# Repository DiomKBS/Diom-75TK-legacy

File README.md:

# full-board-shorter
a keyboard with 75% layout that has macrokeys and a numpad

## The current design:

## You can visit the whiteboard over at Milanote:
Link --> [Whiteboard](https://app.milanote.com/1NjfUT1bPf1Z3v?p=4XtU1EYbywI)

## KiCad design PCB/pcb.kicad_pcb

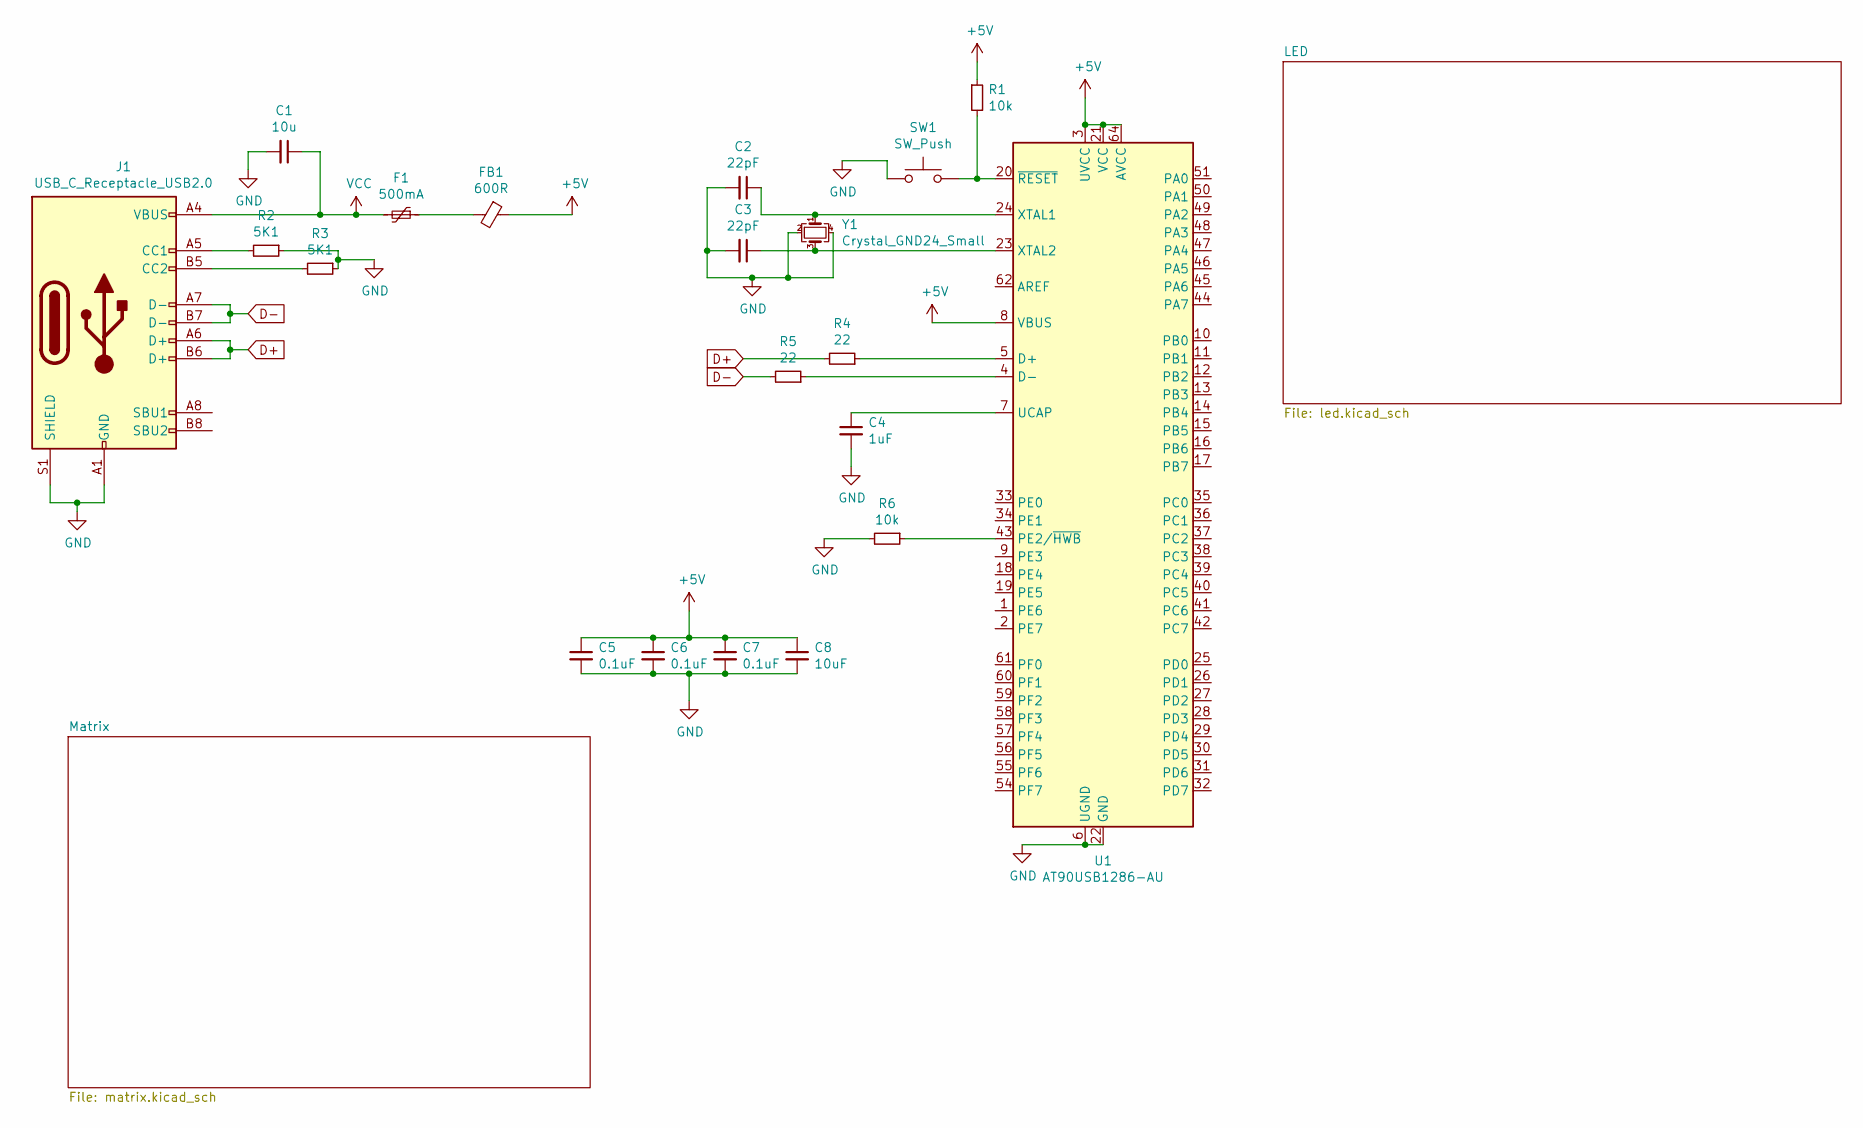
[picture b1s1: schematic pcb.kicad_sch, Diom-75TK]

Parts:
C1: 10u; C_0805_2012Metric
C2, C3: 22pF; C_0805_2012Metric
C4: 1uF; C_0805_2012Metric
C5, C6, C7: 0.1uF; C_0805_2012Metric
C8: 10uF; C_0805_2012Metric
F1: 500mA; Fuse_1206_3216Metric
FB1: 600R; Ferrite_Bead_0603
J1: USB_C_Receptacle_USB2.0; USB_C_Receptacle_HRO_TYPE-C-31-M-12
R1, R6: 10k; R_0805_2012Metric
R2, R3: 5K1; R_0805_2012Metric
R4, R5: 22; R_0805_2012Metric
SW1: SW_Push; switch_without_switch
U1: AT90USB1286-AU; TQFP-64_14x14mm_P0.8mm
Y1: Crystal_GND24_Small; Crystal_SMD_3225-4Pin_3.2x2.5mm

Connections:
+5V: C5.1, C6.1, C7.1, C8.1, FB1.1, R1.1, U1.3 (UVCC), U1.8 (VBUS), U1.21 (VCC), U1.52 (VCC), U1.64 (AVCC); also elsewhere on the board
D+: J1.A6 (D+), J1.B6 (D+), R4.2
D-: J1.A7 (D-), J1.B7 (D-), R5.2
GND: C1.2, C2.2, C3.2, C4.2, C5.2, C6.2, C7.2, C8.2, J1.A1 (GND), J1.A12 (GND), J1.B1 (GND), J1.B12 (GND), J1.S1 (SHIELD), R2.1, R3.1, R6.2, SW1.1, U1.6 (UGND), U1.22 (GND), U1.53 (GND), U1.63 (GND), Y1.2, Y1.4; also elsewhere on the board
unnamed: C2.1, U1.24 (XTAL1), Y1.1
unnamed: C3.1, U1.23 (XTAL2), Y1.3
unnamed: C4.1, U1.7 (UCAP)
unnamed: F1.1, FB1.2
unnamed: J1.A5 (CC1), R2.2
unnamed: J1.B5 (CC2), R3.2
unnamed: R1.2, SW1.2, U1.20 (~RESET)
unnamed: R4.1, U1.5 (D+)
unnamed: R5.1, U1.4 (D-)
unnamed: R6.1, U1.43 (PE2/~HWB)
VCC: C1.1, F1.2, J1.A4 (VBUS), J1.A9 (VBUS), J1.B4 (VBUS), J1.B9 (VBUS)

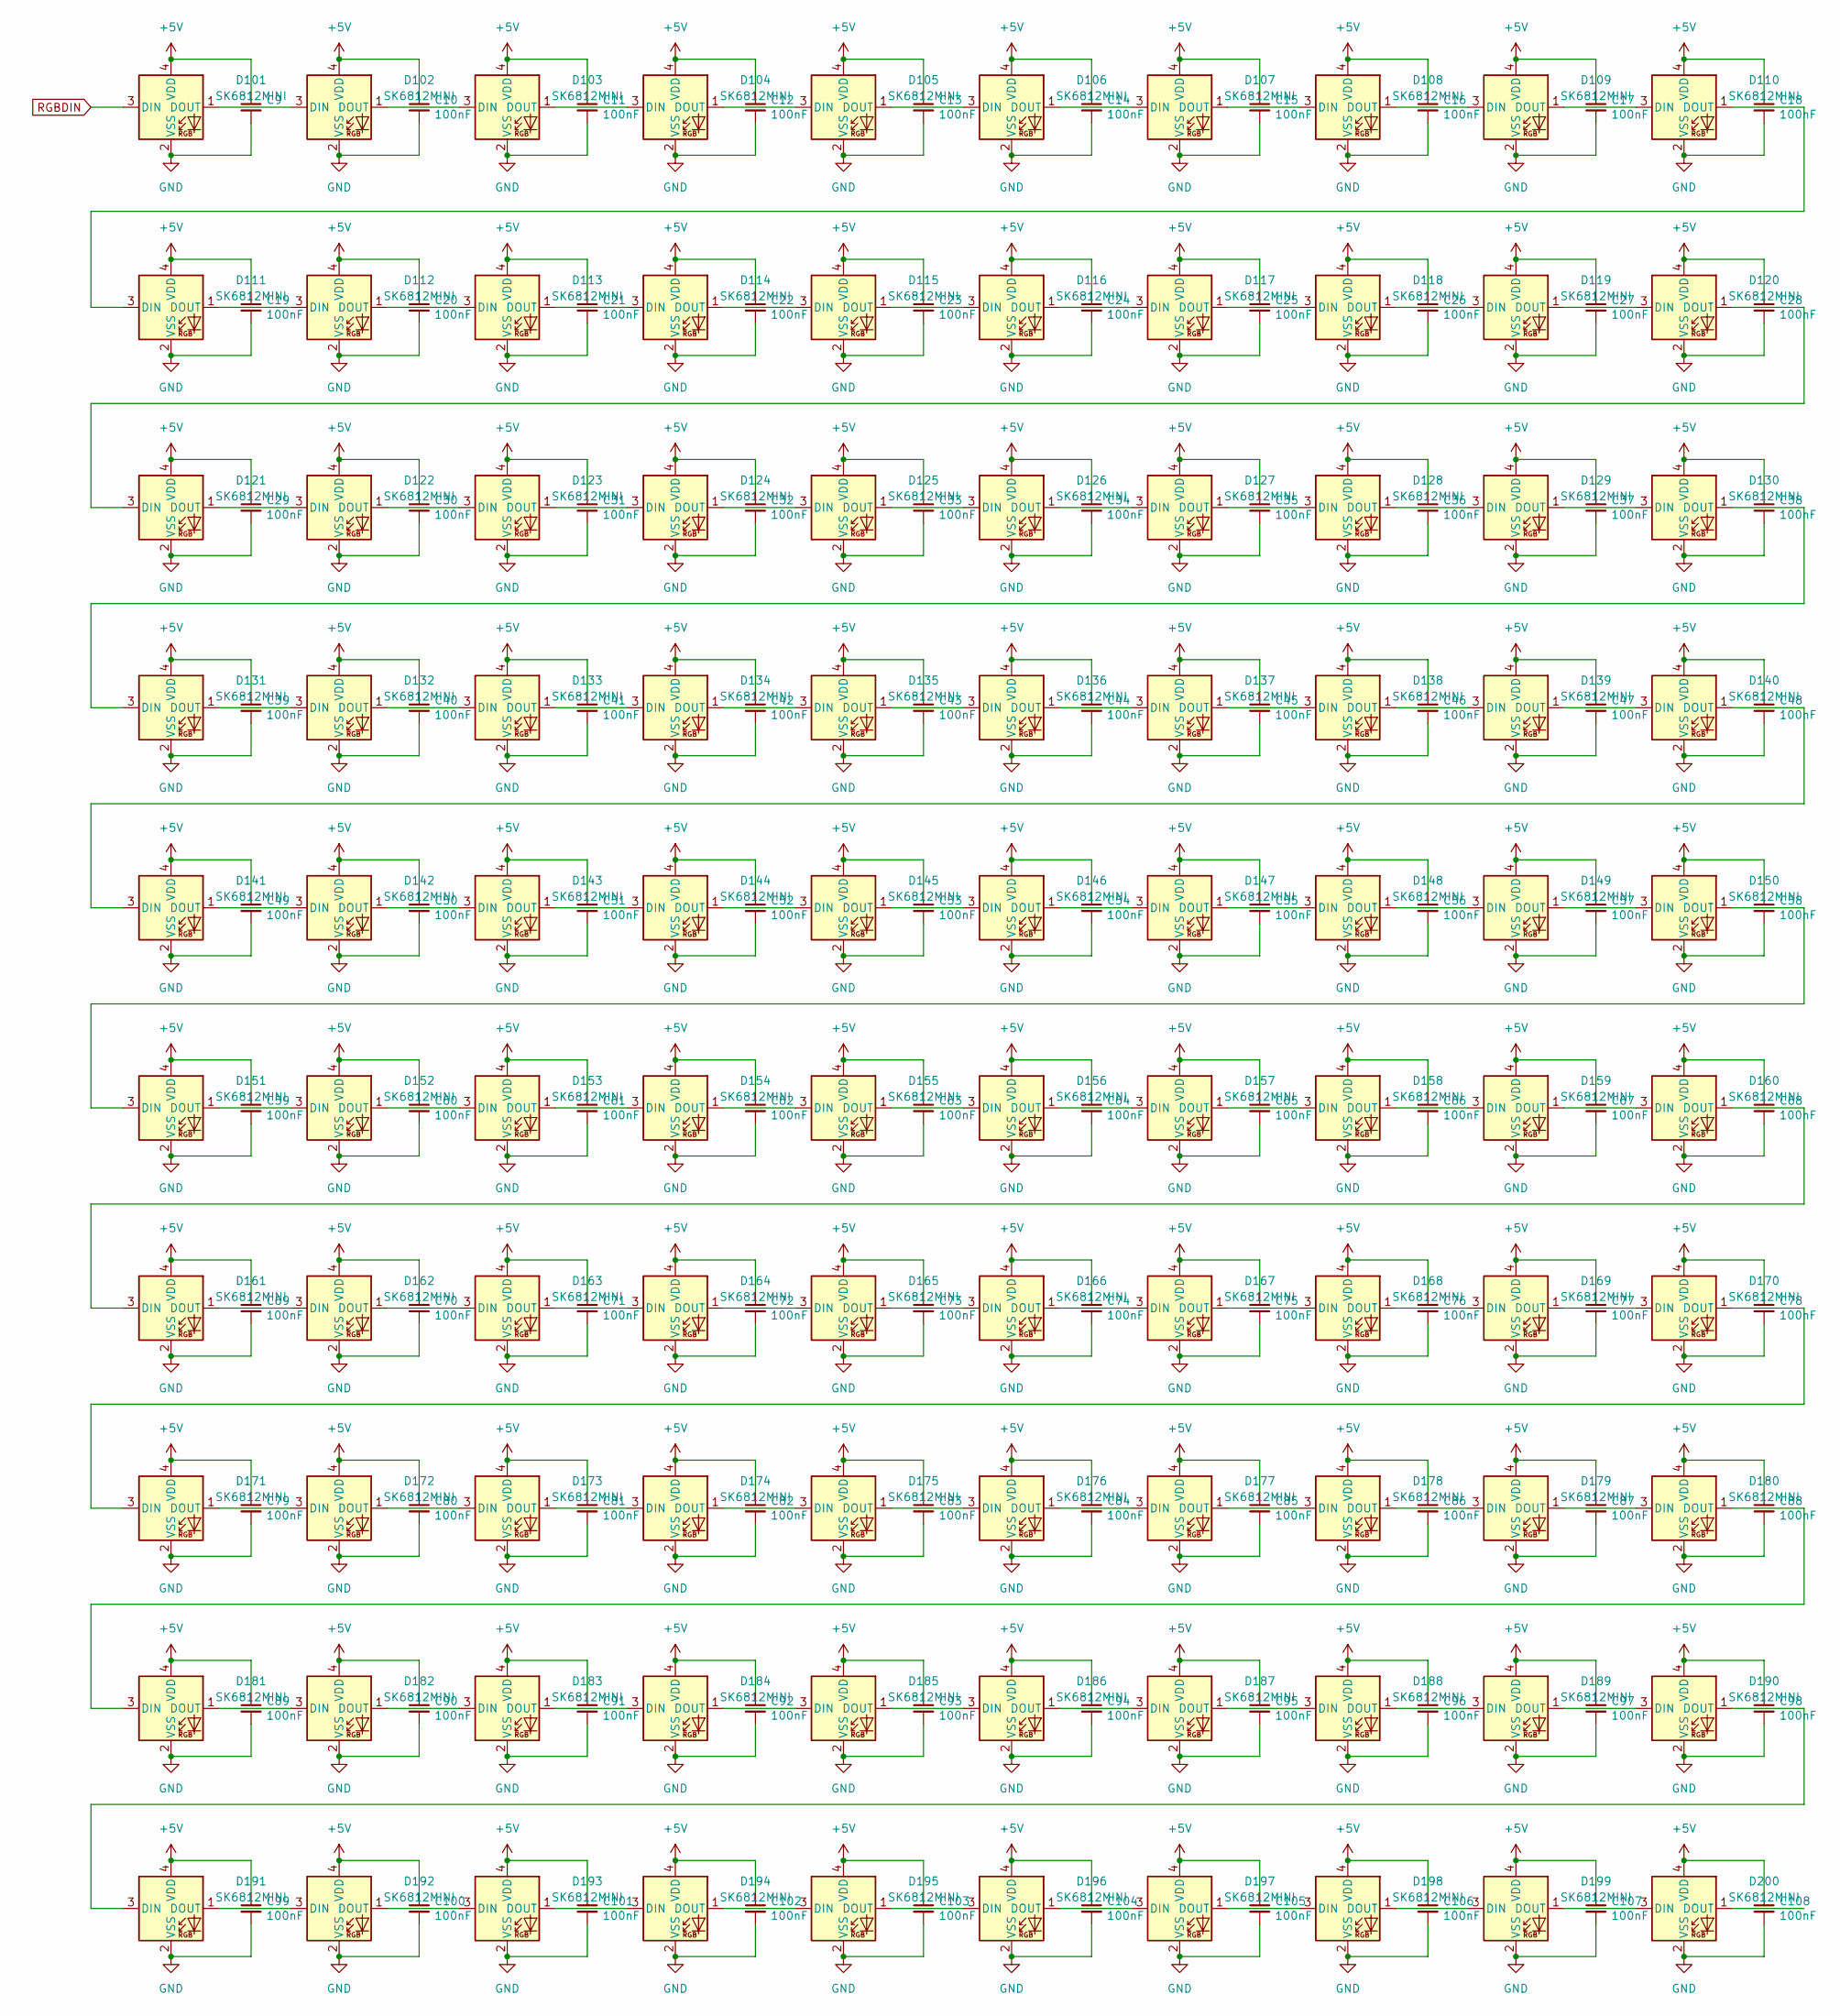
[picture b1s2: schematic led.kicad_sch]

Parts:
C9: (no value)
C10, C11, C12, C13, C14, C15, C16, C17, C18, C19, C20, C21, C22, C23, C24, C25, C26, C27, C28, C29, C30, C31, C32, C33, C34, C35, C36, C37, C38, C39, C40, C41, C42, C43, C44, C45, C46, C47, C48, C49, C50, C51, C52, C53, C54, C55, C56, C57, C58, C59, C60, C61, C62, C63, C64, C65, C66, C67, C68, C69, C70, C71, C72, C73, C74, C75, C76, C77, C78, C79, C80, C81, C82, C83, C84, C85, C86, C87, C88, C89, C90, C91, C92, C93, C94, C95, C96, C97, C98, C99, C100, C101, C102, C103, C104, C105, C106, C107, C108: 100nF
D101, D102, D103, D104, D105, D106, D107, D108, D109, D110, D111, D112, D113, D114, D115, D116, D117, D118, D119, D120, D121, D122, D123, D124, D125, D126, D127, D128, D129, D130, D131, D132, D133, D134, D135, D136, D137, D138, D139, D140, D141, D142, D143, D144, D145, D146, D147, D148, D149, D150, D151, D152, D153, D154, D155, D156, D157, D158, D159, D160, D161, D162, D163, D164, D165, D166, D167, D168, D169, D170, D171, D172, D173, D174, D175, D176, D177, D178, D179, D180, D181, D182, D183, D184, D185, D186, D187, D188, D189, D190, D191, D192, D193, D194, D195, D196, D197, D198, D199, D200: SK6812MINI; SK6812MINI_3.5x3.7mm_SMD-Flipped-Back

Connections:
+5V: C9.1, C10.1, C11.1, C12.1, C13.1, C14.1, C15.1, C16.1, C17.1, C18.1, C19.1, C20.1, C21.1, C22.1, C23.1, C24.1, C25.1, C26.1, C27.1, C28.1, C29.1, C30.1, C31.1, C32.1, C33.1, C34.1, C35.1, C36.1, C37.1, C38.1, C39.1, C40.1, C41.1, C42.1, C43.1, C44.1, C45.1, C46.1, C47.1, C48.1, C49.1, C50.1, C51.1, C52.1, C53.1, C54.1, C55.1, C56.1, C57.1, C58.1, C59.1, C60.1, C61.1, C62.1, C63.1, C64.1, C65.1, C66.1, C67.1, C68.1, C69.1, C70.1, C71.1, C72.1, C73.1, C74.1, C75.1, C76.1, C77.1, C78.1, C79.1, C80.1, C81.1, C82.1, C83.1, C84.1, C85.1, C86.1, C87.1, C88.1, C89.1, C90.1, C91.1, C92.1, C93.1, C94.1, C95.1, C96.1, C97.1, C98.1, C99.1, C100.1, C101.1, C102.1, C103.1, C104.1, C105.1, C106.1, C107.1, C108.1, D101.4 (VDD), D102.4 (VDD), D103.4 (VDD), D104.4 (VDD), D105.4 (VDD), D106.4 (VDD), D107.4 (VDD), D108.4 (VDD), D109.4 (VDD), D110.4 (VDD), D111.4 (VDD), D112.4 (VDD), D113.4 (VDD), D114.4 (VDD), D115.4 (VDD), D116.4 (VDD), D117.4 (VDD), D118.4 (VDD), D119.4 (VDD), D120.4 (VDD), D121.4 (VDD), D122.4 (VDD), D123.4 (VDD), D124.4 (VDD), D125.4 (VDD), D126.4 (VDD), D127.4 (VDD), D128.4 (VDD), D129.4 (VDD), D130.4 (VDD), D131.4 (VDD), D132.4 (VDD), D133.4 (VDD), D134.4 (VDD), D135.4 (VDD), D136.4 (VDD), D137.4 (VDD), D138.4 (VDD), D139.4 (VDD), D140.4 (VDD), D141.4 (VDD), D142.4 (VDD), D143.4 (VDD), D144.4 (VDD), D145.4 (VDD), D146.4 (VDD), D147.4 (VDD), D148.4 (VDD), D149.4 (VDD), D150.4 (VDD), D151.4 (VDD), D152.4 (VDD), D153.4 (VDD), D154.4 (VDD), D155.4 (VDD), D156.4 (VDD), D157.4 (VDD), D158.4 (VDD), D159.4 (VDD), D160.4 (VDD), D161.4 (VDD), D162.4 (VDD), D163.4 (VDD), D164.4 (VDD), D165.4 (VDD), D166.4 (VDD), D167.4 (VDD), D168.4 (VDD), D169.4 (VDD), D170.4 (VDD), D171.4 (VDD), D172.4 (VDD), D173.4 (VDD), D174.4 (VDD), D175.4 (VDD), D176.4 (VDD), D177.4 (VDD), D178.4 (VDD), D179.4 (VDD), D180.4 (VDD), D181.4 (VDD), D182.4 (VDD), D183.4 (VDD), D184.4 (VDD), D185.4 (VDD), D186.4 (VDD), D187.4 (VDD), D188.4 (VDD), D189.4 (VDD), D190.4 (VDD), D191.4 (VDD), D192.4 (VDD), D193.4 (VDD), D194.4 (VDD), D195.4 (VDD), D196.4 (VDD), D197.4 (VDD), D198.4 (VDD), D199.4 (VDD), D200.4 (VDD); also elsewhere on the board
GND: C9.2, C10.2, C11.2, C12.2, C13.2, C14.2, C15.2, C16.2, C17.2, C18.2, C19.2, C20.2, C21.2, C22.2, C23.2, C24.2, C25.2, C26.2, C27.2, C28.2, C29.2, C30.2, C31.2, C32.2, C33.2, C34.2, C35.2, C36.2, C37.2, C38.2, C39.2, C40.2, C41.2, C42.2, C43.2, C44.2, C45.2, C46.2, C47.2, C48.2, C49.2, C50.2, C51.2, C52.2, C53.2, C54.2, C55.2, C56.2, C57.2, C58.2, C59.2, C60.2, C61.2, C62.2, C63.2, C64.2, C65.2, C66.2, C67.2, C68.2, C69.2, C70.2, C71.2, C72.2, C73.2, C74.2, C75.2, C76.2, C77.2, C78.2, C79.2, C80.2, C81.2, C82.2, C83.2, C84.2, C85.2, C86.2, C87.2, C88.2, C89.2, C90.2, C91.2, C92.2, C93.2, C94.2, C95.2, C96.2, C97.2, C98.2, C99.2, C100.2, C101.2, C102.2, C103.2, C104.2, C105.2, C106.2, C107.2, C108.2, D101.2 (VSS), D102.2 (VSS), D103.2 (VSS), D104.2 (VSS), D105.2 (VSS), D106.2 (VSS), D107.2 (VSS), D108.2 (VSS), D109.2 (VSS), D110.2 (VSS), D111.2 (VSS), D112.2 (VSS), D113.2 (VSS), D114.2 (VSS), D115.2 (VSS), D116.2 (VSS), D117.2 (VSS), D118.2 (VSS), D119.2 (VSS), D120.2 (VSS), D121.2 (VSS), D122.2 (VSS), D123.2 (VSS), D124.2 (VSS), D125.2 (VSS), D126.2 (VSS), D127.2 (VSS), D128.2 (VSS), D129.2 (VSS), D130.2 (VSS), D131.2 (VSS), D132.2 (VSS), D133.2 (VSS), D134.2 (VSS), D135.2 (VSS), D136.2 (VSS), D137.2 (VSS), D138.2 (VSS), D139.2 (VSS), D140.2 (VSS), D141.2 (VSS), D142.2 (VSS), D143.2 (VSS), D144.2 (VSS), D145.2 (VSS), D146.2 (VSS), D147.2 (VSS), D148.2 (VSS), D149.2 (VSS), D150.2 (VSS), D151.2 (VSS), D152.2 (VSS), D153.2 (VSS), D154.2 (VSS), D155.2 (VSS), D156.2 (VSS), D157.2 (VSS), D158.2 (VSS), D159.2 (VSS), D160.2 (VSS), D161.2 (VSS), D162.2 (VSS), D163.2 (VSS), D164.2 (VSS), D165.2 (VSS), D166.2 (VSS), D167.2 (VSS), D168.2 (VSS), D169.2 (VSS), D170.2 (VSS), D171.2 (VSS), D172.2 (VSS), D173.2 (VSS), D174.2 (VSS), D175.2 (VSS), D176.2 (VSS), D177.2 (VSS), D178.2 (VSS), D179.2 (VSS), D180.2 (VSS), D181.2 (VSS), D182.2 (VSS), D183.2 (VSS), D184.2 (VSS), D185.2 (VSS), D186.2 (VSS), D187.2 (VSS), D188.2 (VSS), D189.2 (VSS), D190.2 (VSS), D191.2 (VSS), D192.2 (VSS), D193.2 (VSS), D194.2 (VSS), D195.2 (VSS), D196.2 (VSS), D197.2 (VSS), D198.2 (VSS), D199.2 (VSS), D200.2 (VSS); also elsewhere on the board
unnamed: D101.1 (DOUT), D102.3 (DIN)
unnamed: D102.1 (DOUT), D103.3 (DIN)
unnamed: D103.1 (DOUT), D104.3 (DIN)
unnamed: D104.1 (DOUT), D105.3 (DIN)
unnamed: D105.1 (DOUT), D106.3 (DIN)
unnamed: D106.1 (DOUT), D107.3 (DIN)
unnamed: D107.1 (DOUT), D108.3 (DIN)
unnamed: D108.1 (DOUT), D109.3 (DIN)
unnamed: D109.1 (DOUT), D110.3 (DIN)
unnamed: D110.1 (DOUT), D111.3 (DIN)
unnamed: D111.1 (DOUT), D112.3 (DIN)
unnamed: D112.1 (DOUT), D113.3 (DIN)
unnamed: D113.1 (DOUT), D114.3 (DIN)
unnamed: D114.1 (DOUT), D115.3 (DIN)
unnamed: D115.1 (DOUT), D116.3 (DIN)
unnamed: D116.1 (DOUT), D117.3 (DIN)
unnamed: D117.1 (DOUT), D118.3 (DIN)
unnamed: D118.1 (DOUT), D119.3 (DIN)
unnamed: D119.1 (DOUT), D120.3 (DIN)
unnamed: D120.1 (DOUT), D121.3 (DIN)
unnamed: D121.1 (DOUT), D122.3 (DIN)
unnamed: D122.1 (DOUT), D123.3 (DIN)
unnamed: D123.1 (DOUT), D124.3 (DIN)
unnamed: D124.1 (DOUT), D125.3 (DIN)
unnamed: D125.1 (DOUT), D126.3 (DIN)
unnamed: D126.1 (DOUT), D127.3 (DIN)
unnamed: D127.1 (DOUT), D128.3 (DIN)
unnamed: D128.1 (DOUT), D129.3 (DIN)
unnamed: D129.1 (DOUT), D130.3 (DIN)
unnamed: D130.1 (DOUT), D131.3 (DIN)
unnamed: D131.1 (DOUT), D132.3 (DIN)
unnamed: D132.1 (DOUT), D133.3 (DIN)
unnamed: D133.1 (DOUT), D134.3 (DIN)
unnamed: D134.1 (DOUT), D135.3 (DIN)
unnamed: D135.1 (DOUT), D136.3 (DIN)
unnamed: D136.1 (DOUT), D137.3 (DIN)
unnamed: D137.1 (DOUT), D138.3 (DIN)
unnamed: D138.1 (DOUT), D139.3 (DIN)
unnamed: D139.1 (DOUT), D140.3 (DIN)
unnamed: D140.1 (DOUT), D141.3 (DIN)
unnamed: D141.1 (DOUT), D142.3 (DIN)
unnamed: D142.1 (DOUT), D143.3 (DIN)
unnamed: D143.1 (DOUT), D144.3 (DIN)
unnamed: D144.1 (DOUT), D145.3 (DIN)
unnamed: D145.1 (DOUT), D146.3 (DIN)
unnamed: D146.1 (DOUT), D147.3 (DIN)
unnamed: D147.1 (DOUT), D148.3 (DIN)
unnamed: D148.1 (DOUT), D149.3 (DIN)
unnamed: D149.1 (DOUT), D150.3 (DIN)
unnamed: D150.1 (DOUT), D151.3 (DIN)
unnamed: D151.1 (DOUT), D152.3 (DIN)
unnamed: D152.1 (DOUT), D153.3 (DIN)
unnamed: D153.1 (DOUT), D154.3 (DIN)
unnamed: D154.1 (DOUT), D155.3 (DIN)
unnamed: D155.1 (DOUT), D156.3 (DIN)
unnamed: D156.1 (DOUT), D157.3 (DIN)
unnamed: D157.1 (DOUT), D158.3 (DIN)
unnamed: D158.1 (DOUT), D159.3 (DIN)
unnamed: D159.1 (DOUT), D160.3 (DIN)
unnamed: D160.1 (DOUT), D161.3 (DIN)
unnamed: D161.1 (DOUT), D162.3 (DIN)
unnamed: D162.1 (DOUT), D163.3 (DIN)
unnamed: D163.1 (DOUT), D164.3 (DIN)
unnamed: D164.1 (DOUT), D165.3 (DIN)
unnamed: D165.1 (DOUT), D166.3 (DIN)
unnamed: D166.1 (DOUT), D167.3 (DIN)
unnamed: D167.1 (DOUT), D168.3 (DIN)
unnamed: D168.1 (DOUT), D169.3 (DIN)
unnamed: D169.1 (DOUT), D170.3 (DIN)
unnamed: D170.1 (DOUT), D171.3 (DIN)
unnamed: D171.1 (DOUT), D172.3 (DIN)
unnamed: D172.1 (DOUT), D173.3 (DIN)
unnamed: D173.1 (DOUT), D174.3 (DIN)
unnamed: D174.1 (DOUT), D175.3 (DIN)
unnamed: D175.1 (DOUT), D176.3 (DIN)
unnamed: D176.1 (DOUT), D177.3 (DIN)
unnamed: D177.1 (DOUT), D178.3 (DIN)
unnamed: D178.1 (DOUT), D179.3 (DIN)
unnamed: D179.1 (DOUT), D180.3 (DIN)
unnamed: D180.1 (DOUT), D181.3 (DIN)
unnamed: D181.1 (DOUT), D182.3 (DIN)
unnamed: D182.1 (DOUT), D183.3 (DIN)
unnamed: D183.1 (DOUT), D184.3 (DIN)
unnamed: D184.1 (DOUT), D185.3 (DIN)
unnamed: D185.1 (DOUT), D186.3 (DIN)
unnamed: D186.1 (DOUT), D187.3 (DIN)
unnamed: D187.1 (DOUT), D188.3 (DIN)
unnamed: D188.1 (DOUT), D189.3 (DIN)
unnamed: D189.1 (DOUT), D190.3 (DIN)
unnamed: D190.1 (DOUT), D191.3 (DIN)
unnamed: D191.1 (DOUT), D192.3 (DIN)
unnamed: D192.1 (DOUT), D193.3 (DIN)
unnamed: D193.1 (DOUT), D194.3 (DIN)
unnamed: D194.1 (DOUT), D195.3 (DIN)
unnamed: D195.1 (DOUT), D196.3 (DIN)
unnamed: D196.1 (DOUT), D197.3 (DIN)
unnamed: D197.1 (DOUT), D198.3 (DIN)
unnamed: D198.1 (DOUT), D199.3 (DIN)
unnamed: D199.1 (DOUT), D200.3 (DIN)
RGBDIN: D101.3 (DIN)

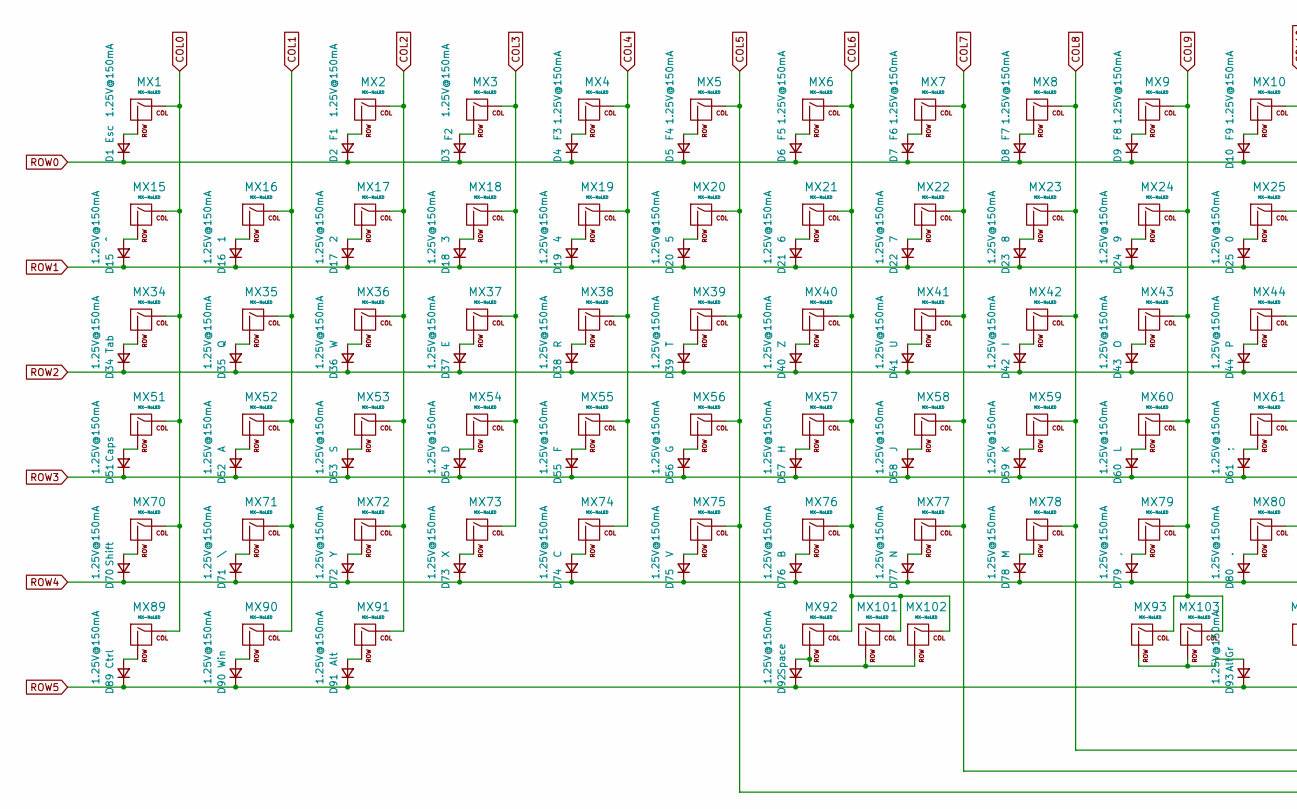
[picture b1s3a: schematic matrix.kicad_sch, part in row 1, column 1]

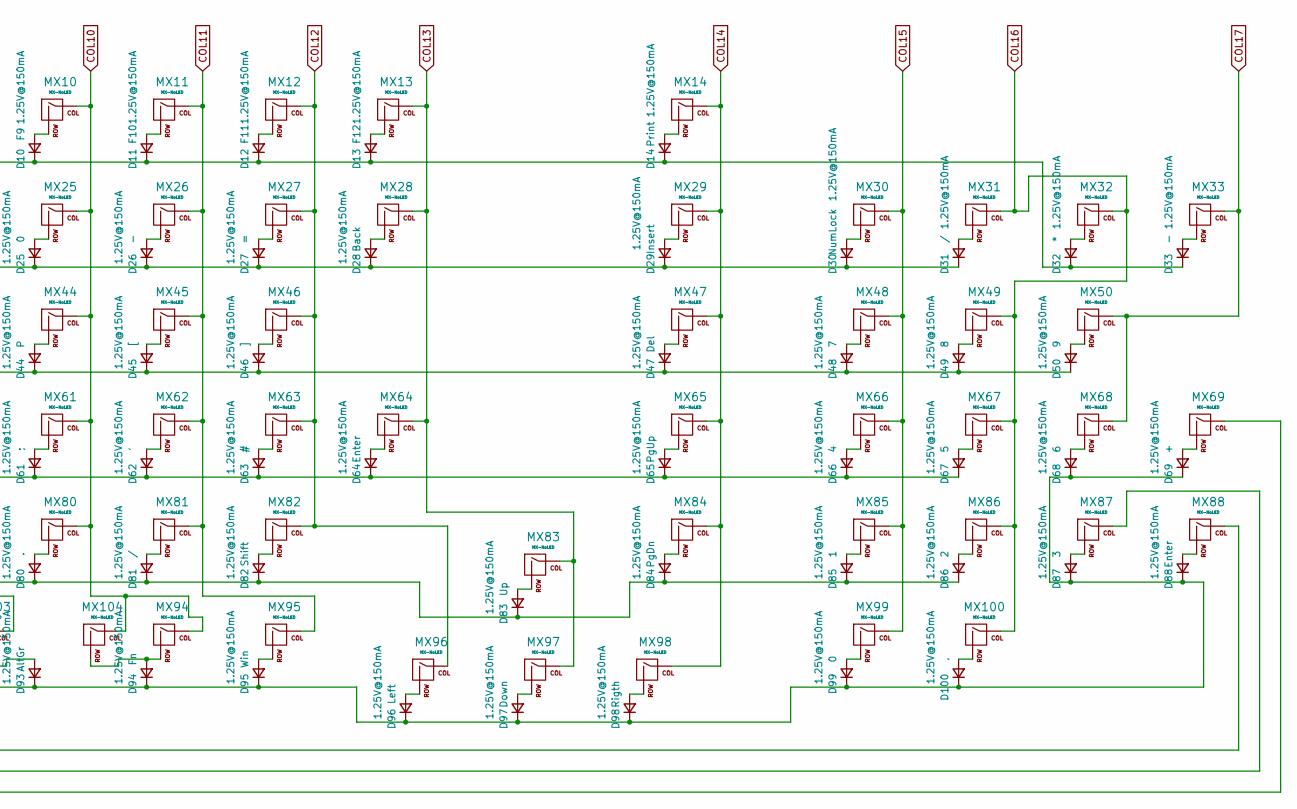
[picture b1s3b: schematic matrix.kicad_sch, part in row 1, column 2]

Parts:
D1, D2, D3, D4, D5, D6, D7, D8, D9, D10, D11, D12, D13, D14, D15, D16, D17, D18, D19, D20, D21, D22, D23, D24, D25, D26, D27, D28, D29, D30, D31, D32, D33, D34, D35, D36, D37, D38, D39, D40, D41, D42, D43, D44, D45, D46, D47, D48, D49, D50, D51, D52, D53, D54, D55, D56, D57, D58, D59, D60, D61, D62, D63, D64, D65, D66, D67, D68, D69, D70, D71, D72, D73, D74, D75, D76, D77, D78, D79, D80, D81, D82, D83, D84, D85, D86, D87, D88, D89, D90, D91, D92, D93, D94, D95, D96, D97, D98, D99, D100: 1.25V@150mA; D_SOD-123
MX1, MX2, MX3, MX4, MX5, MX6, MX7, MX8, MX9, MX10, MX11, MX12, MX13, MX14, MX15, MX16, MX17, MX18, MX19, MX20, MX21, MX22, MX23, MX24, MX25, MX26, MX27, MX29, MX30, MX31, MX32, MX33, MX35, MX36, MX37, MX38, MX39, MX40, MX41, MX42, MX43, MX44, MX45, MX46, MX47, MX48, MX49, MX50, MX52, MX53, MX54, MX55, MX56, MX57, MX58, MX59, MX60, MX61, MX62, MX63, MX65, MX66, MX67, MX68, MX71, MX72, MX73, MX74, MX75, MX76, MX77, MX78, MX79, MX80, MX81, MX83, MX84, MX85, MX86, MX87, MX90, MX94, MX95, MX96, MX97, MX98, MX100, MX103: MX-NoLED; Kailh-Hotswap-1U
MX28, MX99: MX-NoLED; Kailh-Hotswap-2U
MX34, MX89: MX-NoLED; Kailh-Hotswap-1.5U
MX51, MX82: MX-NoLED; Kailh-Hotswap-1.75U
MX64: MX-NoLED; Kailh-Hotswap-EnterISO
MX69, MX88: MX-NoLED; Kailh-Hotswap-2U-Vertical
MX70, MX91, MX93, MX104: MX-NoLED; Kailh-Hotswap-1.25U
MX92: MX-NoLED; Kailh-Hotswap-6U
MX101: MX-NoLED; Kailh-Hotswap-6.25U
MX102: MX-NoLED; Kailh-Hotswap-7U

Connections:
COL0: MX1.1 (COL), MX15.1 (COL), MX34.1 (COL), MX51.1 (COL), MX70.1 (COL), MX89.1 (COL)
COL1: MX16.1 (COL), MX35.1 (COL), MX52.1 (COL), MX71.1 (COL), MX90.1 (COL)
COL2: MX2.1 (COL), MX17.1 (COL), MX36.1 (COL), MX53.1 (COL), MX72.1 (COL), MX91.1 (COL)
COL3: MX3.1 (COL), MX18.1 (COL), MX37.1 (COL), MX54.1 (COL), MX73.1 (COL)
COL4: MX4.1 (COL), MX19.1 (COL), MX38.1 (COL), MX55.1 (COL), MX74.1 (COL)
COL5: MX5.1 (COL), MX20.1 (COL), MX39.1 (COL), MX56.1 (COL), MX69.1 (COL), MX75.1 (COL)
COL6: MX6.1 (COL), MX21.1 (COL), MX40.1 (COL), MX57.1 (COL), MX76.1 (COL), MX92.1 (COL), MX101.1 (COL), MX102.1 (COL)
COL7: MX7.1 (COL), MX22.1 (COL), MX41.1 (COL), MX58.1 (COL), MX77.1 (COL), MX87.1 (COL)
COL8: MX8.1 (COL), MX23.1 (COL), MX42.1 (COL), MX59.1 (COL), MX78.1 (COL), MX88.1 (COL)
COL9: MX9.1 (COL), MX24.1 (COL), MX43.1 (COL), MX60.1 (COL), MX79.1 (COL), MX93.1 (COL), MX103.1 (COL)
COL10: MX10.1 (COL), MX25.1 (COL), MX44.1 (COL), MX61.1 (COL), MX80.1 (COL), MX94.1 (COL), MX104.1 (COL)
COL11: MX11.1 (COL), MX26.1 (COL), MX45.1 (COL), MX62.1 (COL), MX81.1 (COL), MX95.1 (COL)
COL12: MX12.1 (COL), MX27.1 (COL), MX46.1 (COL), MX63.1 (COL), MX82.1 (COL), MX96.1 (COL)
COL13: MX13.1 (COL), MX28.1 (COL), MX64.1 (COL), MX83.1 (COL), MX97.1 (COL)
COL14: MX14.1 (COL), MX29.1 (COL), MX47.1 (COL), MX65.1 (COL), MX84.1 (COL), MX98.1 (COL)
COL15: MX30.1 (COL), MX48.1 (COL), MX66.1 (COL), MX85.1 (COL), MX99.1 (COL)
COL16: MX31.1 (COL), MX32.1 (COL), MX49.1 (COL), MX67.1 (COL), MX86.1 (COL), MX100.1 (COL)
COL17: MX33.1 (COL), MX50.1 (COL), MX68.1 (COL)
unnamed: D1.2 (A), MX1.2 (ROW)
unnamed: D2.2 (A), MX2.2 (ROW)
unnamed: D3.2 (A), MX3.2 (ROW)
unnamed: D4.2 (A), MX4.2 (ROW)
unnamed: D5.2 (A), MX5.2 (ROW)
unnamed: D6.2 (A), MX6.2 (ROW)
unnamed: D7.2 (A), MX7.2 (ROW)
unnamed: D8.2 (A), MX8.2 (ROW)
unnamed: D9.2 (A), MX9.2 (ROW)
unnamed: D10.2 (A), MX10.2 (ROW)
unnamed: D11.2 (A), MX11.2 (ROW)
unnamed: D12.2 (A), MX12.2 (ROW)
unnamed: D13.2 (A), MX13.2 (ROW)
unnamed: D14.2 (A), MX14.2 (ROW)
unnamed: D15.2 (A), MX15.2 (ROW)
unnamed: D16.2 (A), MX16.2 (ROW)
unnamed: D17.2 (A), MX17.2 (ROW)
unnamed: D18.2 (A), MX18.2 (ROW)
unnamed: D19.2 (A), MX19.2 (ROW)
unnamed: D20.2 (A), MX20.2 (ROW)
unnamed: D21.2 (A), MX21.2 (ROW)
unnamed: D22.2 (A), MX22.2 (ROW)
unnamed: D23.2 (A), MX23.2 (ROW)
unnamed: D24.2 (A), MX24.2 (ROW)
unnamed: D25.2 (A), MX25.2 (ROW)
unnamed: D26.2 (A), MX26.2 (ROW)
unnamed: D27.2 (A), MX27.2 (ROW)
unnamed: D28.2 (A), MX28.2 (ROW)
unnamed: D29.2 (A), MX29.2 (ROW)
unnamed: D30.2 (A), MX30.2 (ROW)
unnamed: D31.2 (A), MX31.2 (ROW)
unnamed: D32.2 (A), MX32.2 (ROW)
unnamed: D33.2 (A), MX33.2 (ROW)
unnamed: D34.2 (A), MX34.2 (ROW)
unnamed: D35.2 (A), MX35.2 (ROW)
unnamed: D36.2 (A), MX36.2 (ROW)
unnamed: D37.2 (A), MX37.2 (ROW)
unnamed: D38.2 (A), MX38.2 (ROW)
unnamed: D39.2 (A), MX39.2 (ROW)
unnamed: D40.2 (A), MX40.2 (ROW)
unnamed: D41.2 (A), MX41.2 (ROW)
unnamed: D42.2 (A), MX42.2 (ROW)
unnamed: D43.2 (A), MX43.2 (ROW)
unnamed: D44.2 (A), MX44.2 (ROW)
unnamed: D45.2 (A), MX45.2 (ROW)
unnamed: D46.2 (A), MX46.2 (ROW)
unnamed: D47.2 (A), MX47.2 (ROW)
unnamed: D48.2 (A), MX48.2 (ROW)
unnamed: D49.2 (A), MX49.2 (ROW)
unnamed: D50.2 (A), MX50.2 (ROW)
unnamed: D51.2 (A), MX51.2 (ROW)
unnamed: D52.2 (A), MX52.2 (ROW)
unnamed: D53.2 (A), MX53.2 (ROW)
unnamed: D54.2 (A), MX54.2 (ROW)
unnamed: D55.2 (A), MX55.2 (ROW)
unnamed: D56.2 (A), MX56.2 (ROW)
unnamed: D57.2 (A), MX57.2 (ROW)
unnamed: D58.2 (A), MX58.2 (ROW)
unnamed: D59.2 (A), MX59.2 (ROW)
unnamed: D60.2 (A), MX60.2 (ROW)
unnamed: D61.2 (A), MX61.2 (ROW)
unnamed: D62.2 (A), MX62.2 (ROW)
unnamed: D63.2 (A), MX63.2 (ROW)
unnamed: D64.2 (A), MX64.2 (ROW)
unnamed: D65.2 (A), MX65.2 (ROW)
unnamed: D66.2 (A), MX66.2 (ROW)
unnamed: D67.2 (A), MX67.2 (ROW)
unnamed: D68.2 (A), MX68.2 (ROW)
unnamed: D69.2 (A), MX69.2 (ROW)
unnamed: D70.2 (A), MX70.2 (ROW)
unnamed: D71.2 (A), MX71.2 (ROW)
unnamed: D72.2 (A), MX72.2 (ROW)
unnamed: D73.2 (A), MX73.2 (ROW)
unnamed: D74.2 (A), MX74.2 (ROW)
unnamed: D75.2 (A), MX75.2 (ROW)
unnamed: D76.2 (A), MX76.2 (ROW)
unnamed: D77.2 (A), MX77.2 (ROW)
unnamed: D78.2 (A), MX78.2 (ROW)
unnamed: D79.2 (A), MX79.2 (ROW)
unnamed: D80.2 (A), MX80.2 (ROW)
unnamed: D81.2 (A), MX81.2 (ROW)
unnamed: D82.2 (A), MX82.2 (ROW)
unnamed: D83.2 (A), MX83.2 (ROW)
unnamed: D84.2 (A), MX84.2 (ROW)
unnamed: D85.2 (A), MX85.2 (ROW)
unnamed: D86.2 (A), MX86.2 (ROW)
unnamed: D87.2 (A), MX87.2 (ROW)
unnamed: D88.2 (A), MX88.2 (ROW)
unnamed: D89.2 (A), MX89.2 (ROW)
unnamed: D90.2 (A), MX90.2 (ROW)
unnamed: D91.2 (A), MX91.2 (ROW)
unnamed: D92.2 (A), MX92.2 (ROW), MX101.2 (ROW), MX102.2 (ROW)
unnamed: D93.2 (A), MX93.2 (ROW), MX103.2 (ROW)
unnamed: D94.2 (A), MX94.2 (ROW), MX104.2 (ROW)
unnamed: D95.2 (A), MX95.2 (ROW)
unnamed: D96.2 (A), MX96.2 (ROW)
unnamed: D97.2 (A), MX97.2 (ROW)
unnamed: D98.2 (A), MX98.2 (ROW)
unnamed: D99.2 (A), MX99.2 (ROW)
unnamed: D100.2 (A), MX100.2 (ROW)
ROW0: D1.1 (K), D2.1 (K), D3.1 (K), D4.1 (K), D5.1 (K), D6.1 (K), D7.1 (K), D8.1 (K), D9.1 (K), D10.1 (K), D11.1 (K), D12.1 (K), D13.1 (K), D14.1 (K), D32.1 (K), D33.1 (K)
ROW1: D15.1 (K), D16.1 (K), D17.1 (K), D18.1 (K), D19.1 (K), D20.1 (K), D21.1 (K), D22.1 (K), D23.1 (K), D24.1 (K), D25.1 (K), D26.1 (K), D27.1 (K), D28.1 (K), D29.1 (K), D30.1 (K), D31.1 (K)
ROW2: D34.1 (K), D35.1 (K), D36.1 (K), D37.1 (K), D38.1 (K), D39.1 (K), D40.1 (K), D41.1 (K), D42.1 (K), D43.1 (K), D44.1 (K), D45.1 (K), D46.1 (K), D47.1 (K), D48.1 (K), D49.1 (K), D50.1 (K)
ROW3: D51.1 (K), D52.1 (K), D53.1 (K), D54.1 (K), D55.1 (K), D56.1 (K), D57.1 (K), D58.1 (K), D59.1 (K), D60.1 (K), D61.1 (K), D62.1 (K), D63.1 (K), D64.1 (K), D65.1 (K), D66.1 (K), D67.1 (K)
ROW4: D70.1 (K), D71.1 (K), D72.1 (K), D73.1 (K), D74.1 (K), D75.1 (K), D76.1 (K), D77.1 (K), D78.1 (K), D79.1 (K), D80.1 (K), D81.1 (K), D82.1 (K), D83.1 (K), D84.1 (K), D85.1 (K), D86.1 (K)
ROW5: D68.1 (K), D69.1 (K), D87.1 (K), D88.1 (K), D89.1 (K), D90.1 (K), D91.1 (K), D92.1 (K), D93.1 (K), D94.1 (K), D95.1 (K), D96.1 (K), D97.1 (K), D98.1 (K), D99.1 (K), D100.1 (K)

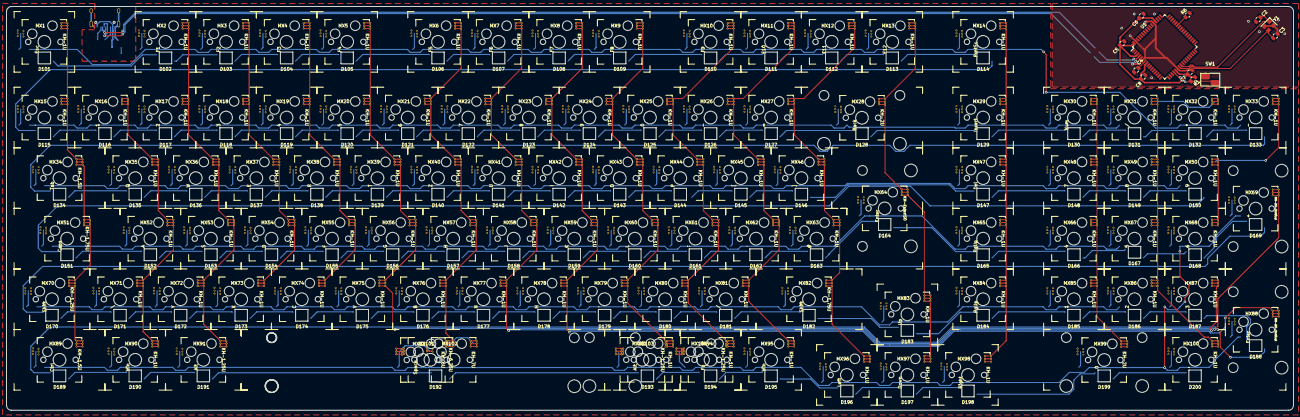
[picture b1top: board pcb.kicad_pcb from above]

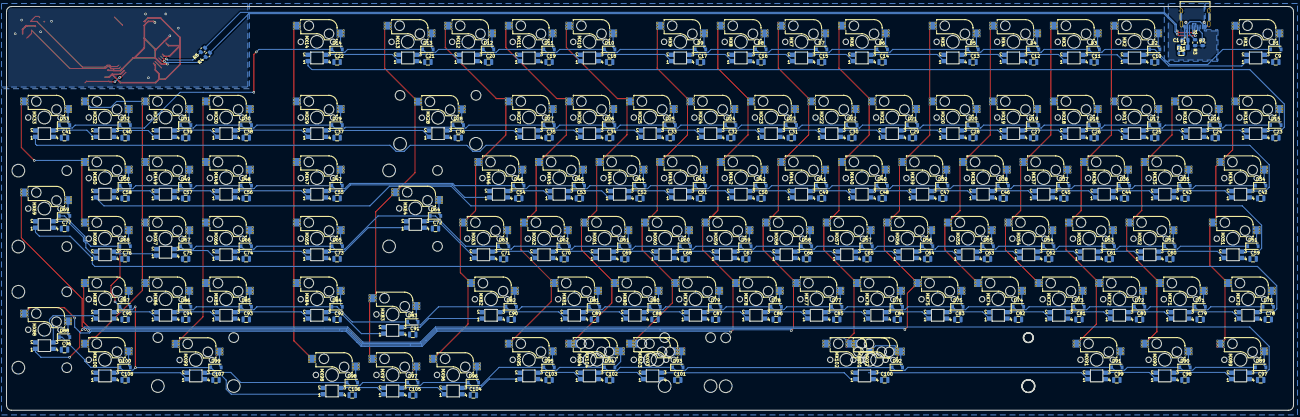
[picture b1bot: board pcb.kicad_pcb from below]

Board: 2 copper layers, 404.8 x 127.0 mm, 424 parts (208 on the bottom side), 238 nets.
